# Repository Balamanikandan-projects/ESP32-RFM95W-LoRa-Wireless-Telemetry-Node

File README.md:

# Custom ESP32 & RFM95W LoRa Wireless Telemetry Node

[Full 3D board render]

A compact, high-performance, **4-layer custom PCB design** integrating an ESP32-WROOM-32E microcontroller with an RFM95W sub-GHz LoRa radio module. This hardware platform is engineered as a robust, low-power remote data acquisition node featuring an optimized power distribution network (PDN) and controlled-impedance RF path layout.

---

## 🚀 Key Features & Architectural Highlights

* **Core Processing:** Powered by an **ESP32-WROOM-32E**, managing application firmware, peripheral communication via SPI/UART, and deep-sleep low-power states.
* **Long-Range RF Connectivity:** Integrated **HOPERF RFM95W LoRa module** mapped over a high-speed synchronous SPI bus for long-range, sub-GHz wireless telemetry.
* **Advanced 4-Layer Stackup:** Engineered with a strict high-speed layout methodology:
  * **Layer 1 (Top):** Signal routing, RF traces, and critical high-frequency component placement.
  * **Layer 2 (Inner 1):** Solid **GND Plane** for low-impedance return paths and EMI shielding.
  * **Layer 3 (Inner 2):** Split **Power Plane** (+3.3V, VBAT, +5V) to ensure low-drop DC distribution.
  * **Layer 4 (Bottom):** Slow-moving control signals, programming buses, and local ground copper fill.
* **Dual-Input Automated Power Path:** Seamless automated power switching between USB Type-C ($5\text{V}$) and a Lithium-Polymer battery ($3.7\text{V} - 4.2\text{V}$) using a low-forward-drop Schottky barrier isolation diode.
* **Integrated Battery Management:** Onboard **TP4056 linear LiPo battery charger** with a programmable constant-current resistor network to regulate charging states safely.
* **High-Transient Power Regulation:** Equipped with a **TLV62569 synchronous buck regulator** providing a rock-solid $+3.3\text{V}$ rail capable of delivering up to $2\text{A}$ to handle active RF and Wi-Fi transmission bursts without voltage sags.

![PCB Layer Stackup Configuration]

---

## 🛠️ Hardware System Architecture & Floorplanning

The physical PCB layout is meticulously split into isolated functional blocks (Islands) to maximize signal integrity and prevent noise coupling:

### 1. Power Input & Charging (Zone 1)
* **USB-C Interface:** Standard 16-pin USB-C receptacle configured with dedicated $5.1\text{k}\Omega$ pull-down resistors on CC1/CC2 lines for downstream power negotiation.
* **Input Filtering:** High-frequency ceramic decoupling capacitors ($10\mu\text{F}$, 0603) placed immediately adjacent to the VBUS pins to suppress transient input ripples.

### 2. DC-DC High-Frequency Switching Regulator (Zone 2)
* **Switching Loop Minimization:** The $2.2\mu\text{H}$ power inductor ($L_1$) and input/output filters are placed directly next to the TLV62569 pads to minimize the high $di/dt$ switching loop area.
* **Isolated Feedback Network:** The voltage divider feedback resistors ($R_4, R_5$) are trace-isolated away from the noisy switching node to prevent output voltage fluctuations.

### 3. Microcontroller & Boot Strapping Constraints (Zone 3)
* **Deterministic Boot Logic:** Hardware pull-up and pull-down networks ($10\text{k}\Omega$) are hardwired on critical strapping pins (`GPIO 0`, `GPIO 5`, `GPIO 15`) to force stable system execution modes during reset and eliminate ambient floating noise.
* **Antenna Edge Clearance:** The ESP32's onboard trace antenna is positioned over a complete physical board overhang keepout zone, keeping all 4 copper layers fully clear of planes and traces to ensure 100% radiation efficiency.

### 4. RF Interface & Impedance Matching (Zone 4)
* **Bus Topography:** Parallel high-speed SPI bus routing (`MOSI`, `MISO`, `SCK`, `NSS`) designed with uniform lengths.
* **$50\Omega$ Antenna Path:** A straight-line **Pi-matching network** layout (Shunt C / Series R / Shunt C) routed into an edge-mounted coaxial SMA antenna jack, structured as a controlled $50\Omega$ microstrip transmission line.

### 5. UART Programming Breakout (Zone 5)
* Exposes standard `GND`, `TXD0`, `RXD0`, and `+3.3V` connections via a 4-pin male header for secure interface access using standard external USB-to-UART bridging modules.
![Complete KiCad Schematic Capture]

---

## 📊 Verification, Design Rules & Layout Integrity

* **Electrical Rules Check (ERC):** Achieved a clean **0 Errors / 0 Warnings** baseline in KiCad, eliminating overlapping net labels, unconfigured power pins, or short circuits.
* **Design Rules Check (DRC):** Clean zero-error verification. Surface-mount pad routing challenges (such as USB-C tight mechanical clearances) were bypassed using direct-to-plane localized micro-vias down to the Inner Layer 2 Ground plane, reducing track parasitics and eliminating top-layer signal crowding.
![DRC Clean Pass Window]

---

## 💻 Technical Toolstack
* **EDA Suite:** KiCad (Schematic Capture, Custom Footprint Management, 4-Layer PCB Layout)
* **Component Form Factor:** Optimized using a space-saving $0603$ SMD footprint strategy for passives to secure layout compactness while maintaining manual bench-test and debugging solderability.

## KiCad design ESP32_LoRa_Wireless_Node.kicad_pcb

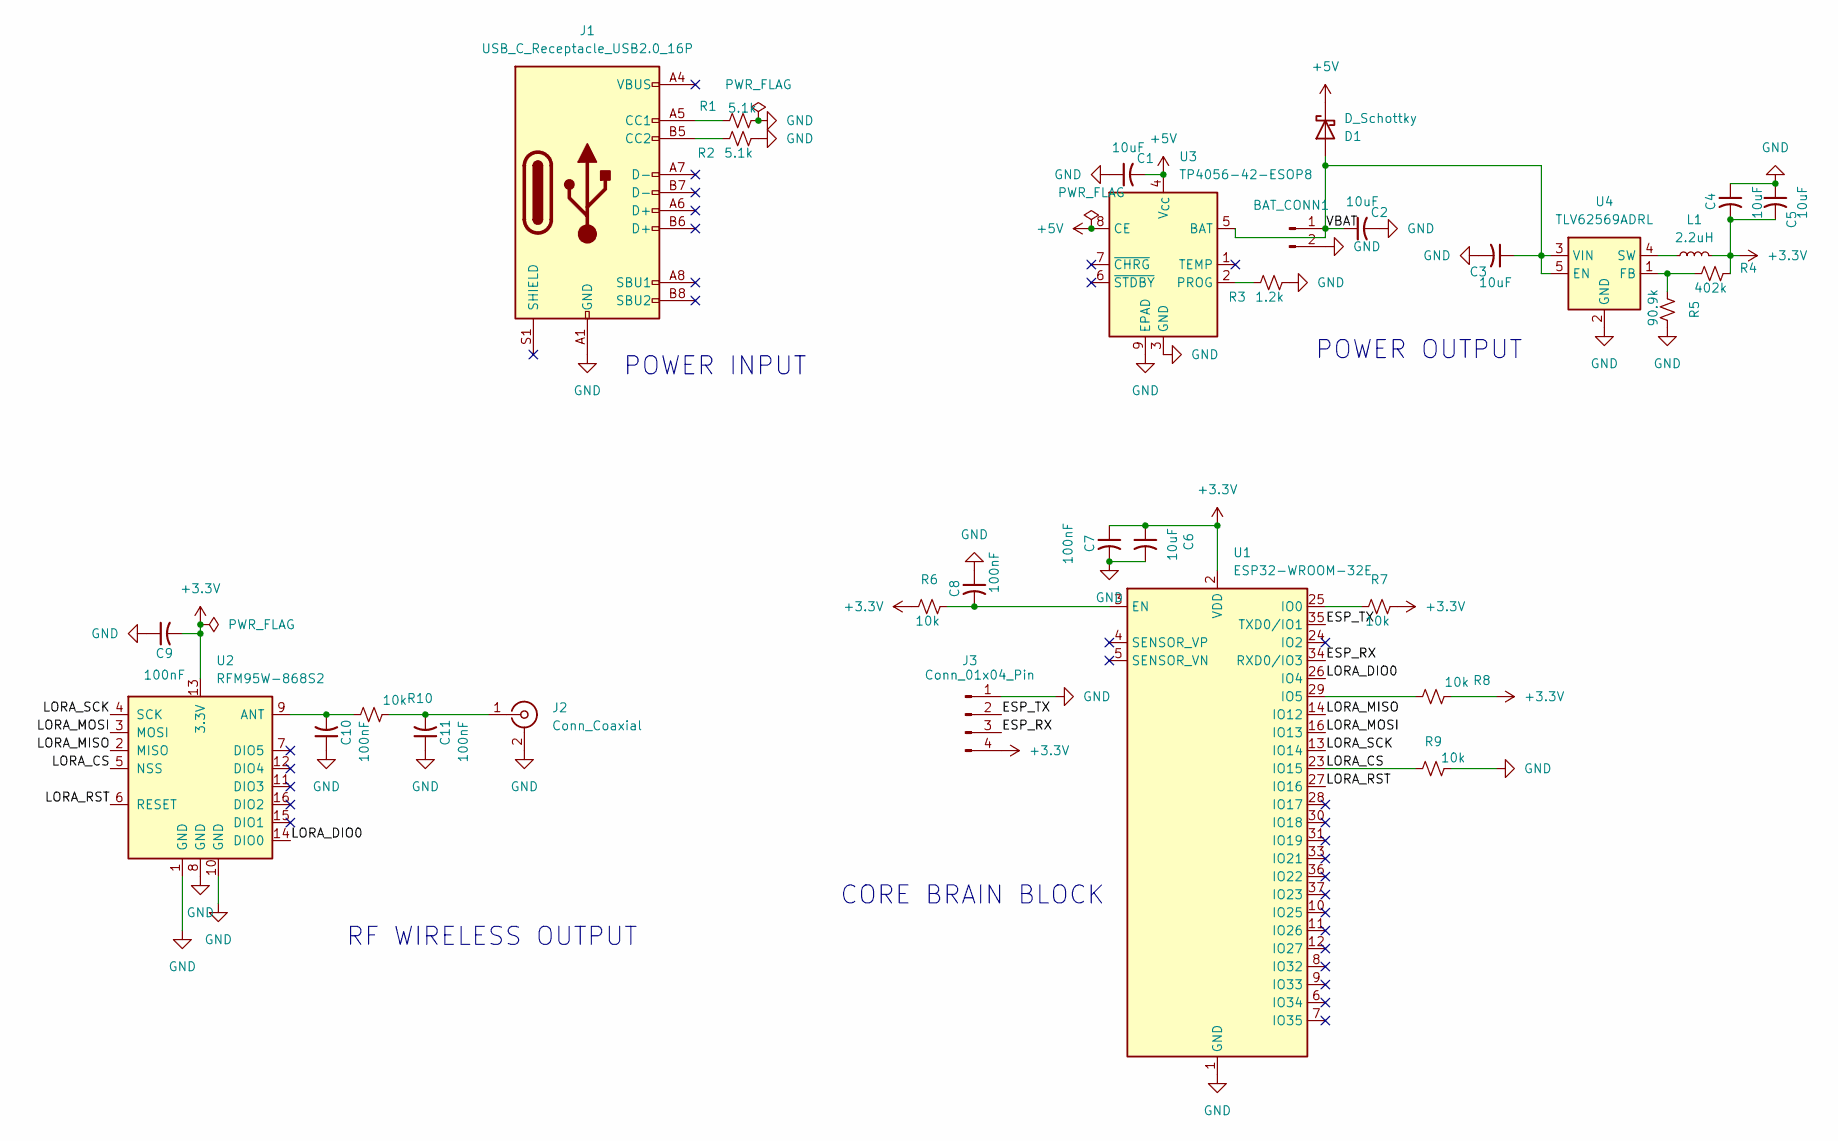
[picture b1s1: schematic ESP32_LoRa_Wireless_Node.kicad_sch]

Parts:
BAT_CONN1: Conn_01x02_Pin; JST_PH_B2B-PH-K_1x02_P2.00mm_Vertical
C1, C2, C3, C4, C5, C6: 10uF; C_0603_1608Metric
C7, C8, C9, C10, C11: 100nF; C_0603_1608Metric
D1: D_Schottky; D_SOD-123
J1: USB_C_Receptacle_USB2.0_16P; USB_C_Receptacle_GCT_USB4085
J2: Conn_Coaxial; SMA_Amphenol_132134_Vertical
J3: Conn_01x04_Pin; PinHeader_1x04_P2.54mm_Vertical
L1: 2.2uH; L_0805_2012Metric
R1, R2: 5.1k; R_0603_1608Metric
R3: 1.2k; R_0603_1608Metric
R4: 402k; R_0603_1608Metric
R5: 90.9k; R_0603_1608Metric
R6, R7, R8, R9, R10: 10k; R_0603_1608Metric
U1: ESP32-WROOM-32E; ESP32-WROOM-32D
U2: RFM95W-868S2; HOPERF_RFM9XW_SMD
U3: TP4056-42-ESOP8; SOIC-8-1EP_3.9x4.9mm_P1.27mm_EP2.41x3.3mm_ThermalVias
U4: TLV62569ADRL; SOT-563

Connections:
+3.3V: C4.2, C5.2, C6.1, C7.1, C9.2, J3.4, L1.2, R4.2, R6.1, R7.2, R8.2, U1.2 (VDD), U2.13 (3.3V)
+5V: C1.2, D1.1 (K), U3.4 (V_{CC}), U3.8 (CE)
/ESP_RX: J3.3, U1.34 (RXD0/IO3)
/ESP_TX: J3.2, U1.35 (TXD0/IO1)
/LORA_CS: R9.1, U1.23 (IO15), U2.5 (NSS)
/LORA_DIO0: U1.26 (IO4), U2.14 (DIO0)
/LORA_MISO: U1.14 (IO12), U2.2 (MISO)
/LORA_MOSI: U1.16 (IO13), U2.3 (MOSI)
/LORA_RST: U1.27 (IO16), U2.6 (RESET)
/LORA_SCK: U1.13 (IO14), U2.4 (SCK)
/VBAT: BAT_CONN1.1, C2.1, C3.1, D1.2 (A), U3.5 (BAT), U4.3 (VIN), U4.5 (EN)
GND: BAT_CONN1.2, C1.1, C2.2, C3.2, C4.1, C5.1, C6.2, C7.2, C8.1, C9.1, C10.1, C11.1, J1.A1 (GND), J1.A12 (GND), J1.B1 (GND), J1.B12 (GND), J2.2 (Ext), J3.1, R1.2, R2.2, R3.2, R5.2, R9.2, U1.1 (GND), U1.15 (GND), U1.38 (GND), U1.39 (GND), U2.1 (GND), U2.8 (GND), U2.10 (GND), U3.3 (GND), U3.9 (EPAD), U4.2 (GND)
unnamed: J1.A5 (CC1), R1.1
unnamed: J1.B5 (CC2), R2.1
unnamed: C11.2, J2.1 (In), R10.2
unnamed: C8.2, R6.2, U1.3 (EN)
unnamed: R7.1, U1.25 (IO0)
unnamed: R8.1, U1.29 (IO5)
unnamed: C10.2, R10.1, U2.9 (ANT)
unnamed: R3.1, U3.2 (PROG)
unnamed: R4.1, R5.1, U4.1 (FB)
unnamed: L1.1, U4.4 (SW)

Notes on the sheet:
POWER INPUT
CORE BRAIN BLOCK
POWER OUTPUT
RF WIRELESS OUTPUT

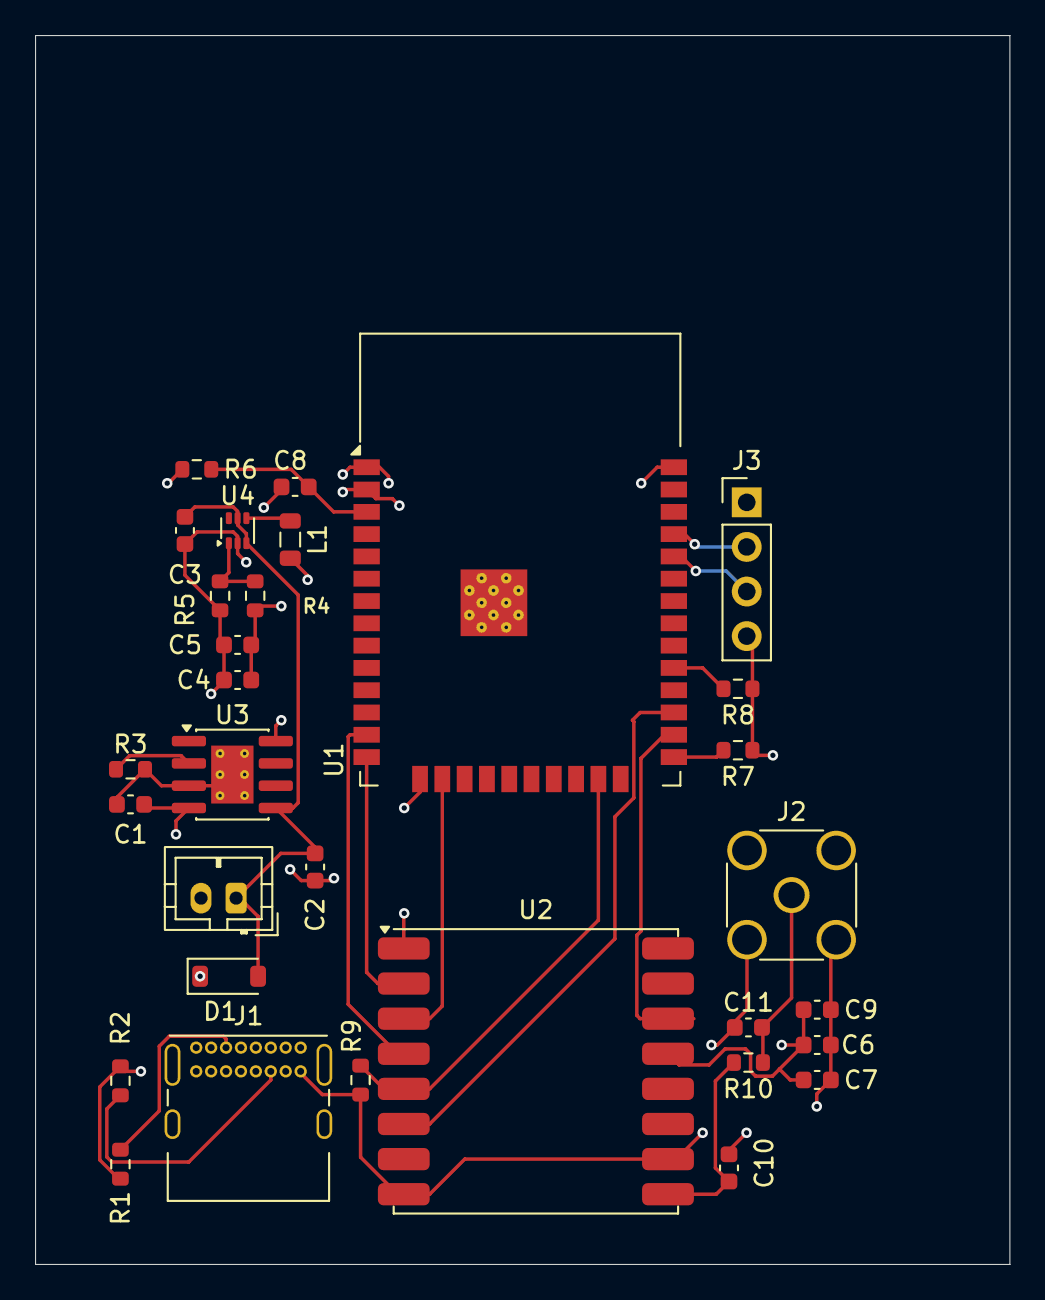
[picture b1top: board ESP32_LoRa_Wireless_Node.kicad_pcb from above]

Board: 4 copper layers, 55.5 x 70.0 mm, 31 parts (0 on the bottom side), 22 nets.
